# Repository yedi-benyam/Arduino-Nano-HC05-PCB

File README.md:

# Arduino Nano + HC-05 Bluetooth PCB (KiCad Project)

## Project Overview
This project is a custom PCB designed using KiCad to interface an Arduino Nano with an HC-05 Bluetooth module. The board enables wireless serial communication using UART and is designed for embedded systems learning and prototyping.

---

## Objectives
- Design a functional embedded system PCB using KiCad
- Interface Arduino Nano with HC-05 Bluetooth module
- Understand UART communication (TX/RX)
- Practice schematic design, PCB layout, and routing
- Generate manufacturing-ready Gerber files

---

## Features
- Arduino Nano R3 based design
- HC-05 Bluetooth module interface (UART communication)
- Power and ground distribution
- Status LED indicators
- Push button input support
- Clean PCB layout for prototyping

---

## Circuit Description
- Arduino Nano communicates with HC-05 using UART:
  - TX → RX
  - RX → TX
- Powered via 5V and GND
- Optional LED indicators for system status

---

## Author
Yedi Benyam

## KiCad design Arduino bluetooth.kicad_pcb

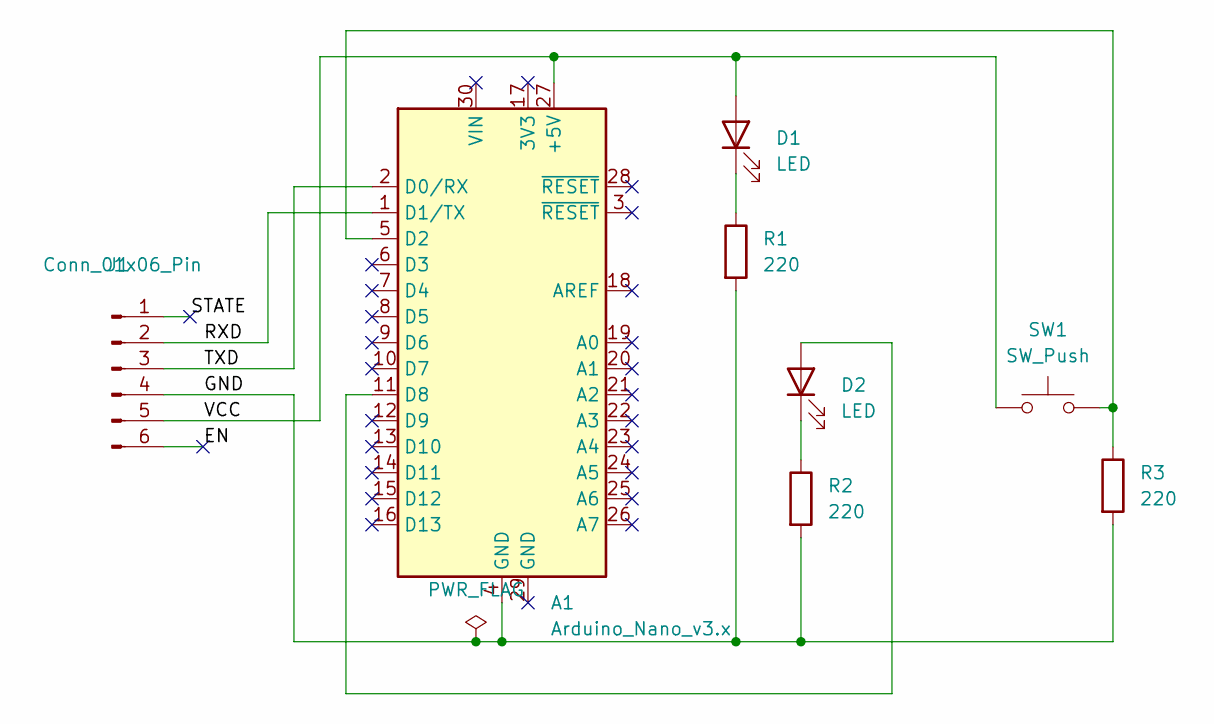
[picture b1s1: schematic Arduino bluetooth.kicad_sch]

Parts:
A1: Arduino_Nano_v3.x; Arduino_Nano
D1, D2: LED; LED_D5.0mm
J1: Conn_01x06_Pin; PinSocket_1x06_P2.54mm_Vertical
R1, R2, R3: 220; R_Axial_DIN0207_L6.3mm_D2.5mm_P7.62mm_Horizontal
SW1: SW_Push; SW_PUSH_6mm

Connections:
/EN: J1.6
/GND: A1.4 (GND), J1.4, R1.2, R2.2, R3.2
/RXD: A1.1 (D1/TX), J1.2
/STATE: J1.1
/TXD: A1.2 (D0/RX), J1.3
/VCC: A1.27 (+5V), D1.2 (A), J1.5, SW1.1
unnamed: A1.5 (D2), R3.1, SW1.2
unnamed: A1.11 (D8), D2.2 (A)
unnamed: D1.1 (K), R1.1
unnamed: D2.1 (K), R2.1

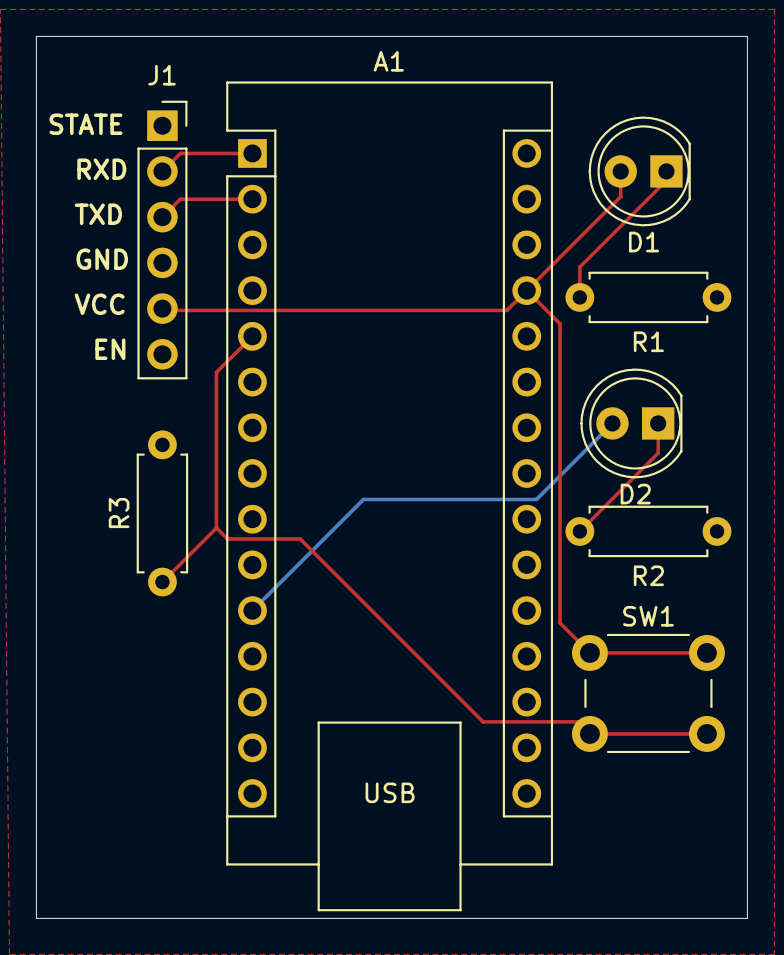
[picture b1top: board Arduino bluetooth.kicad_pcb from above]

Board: 2 copper layers, 39.5 x 49.0 mm, 8 parts (0 on the bottom side), 8 nets.
